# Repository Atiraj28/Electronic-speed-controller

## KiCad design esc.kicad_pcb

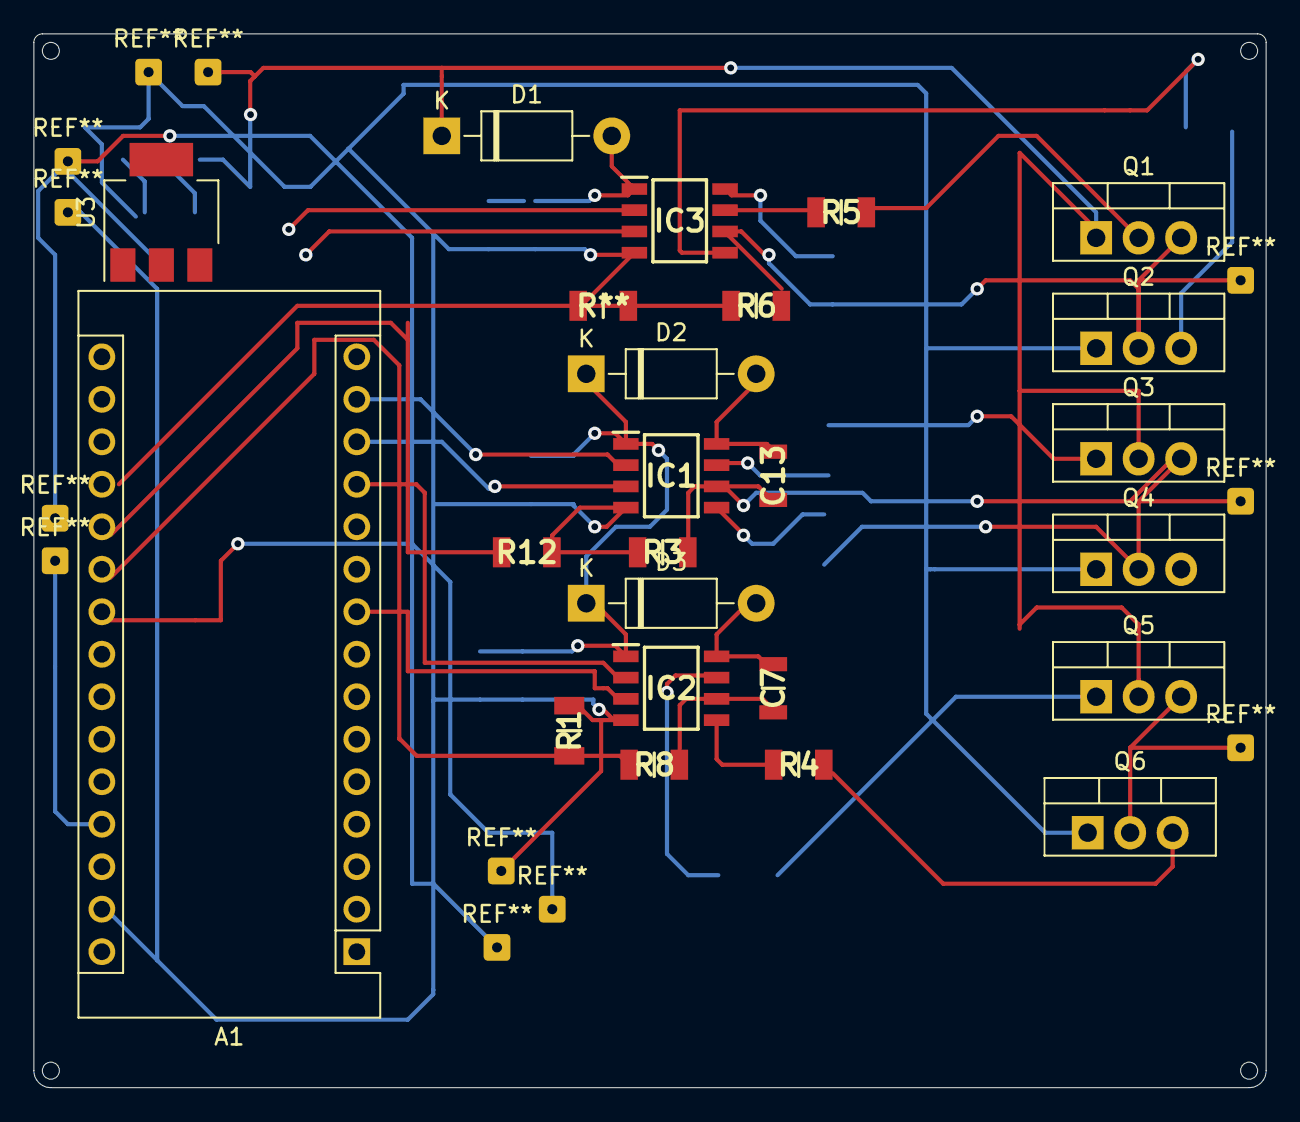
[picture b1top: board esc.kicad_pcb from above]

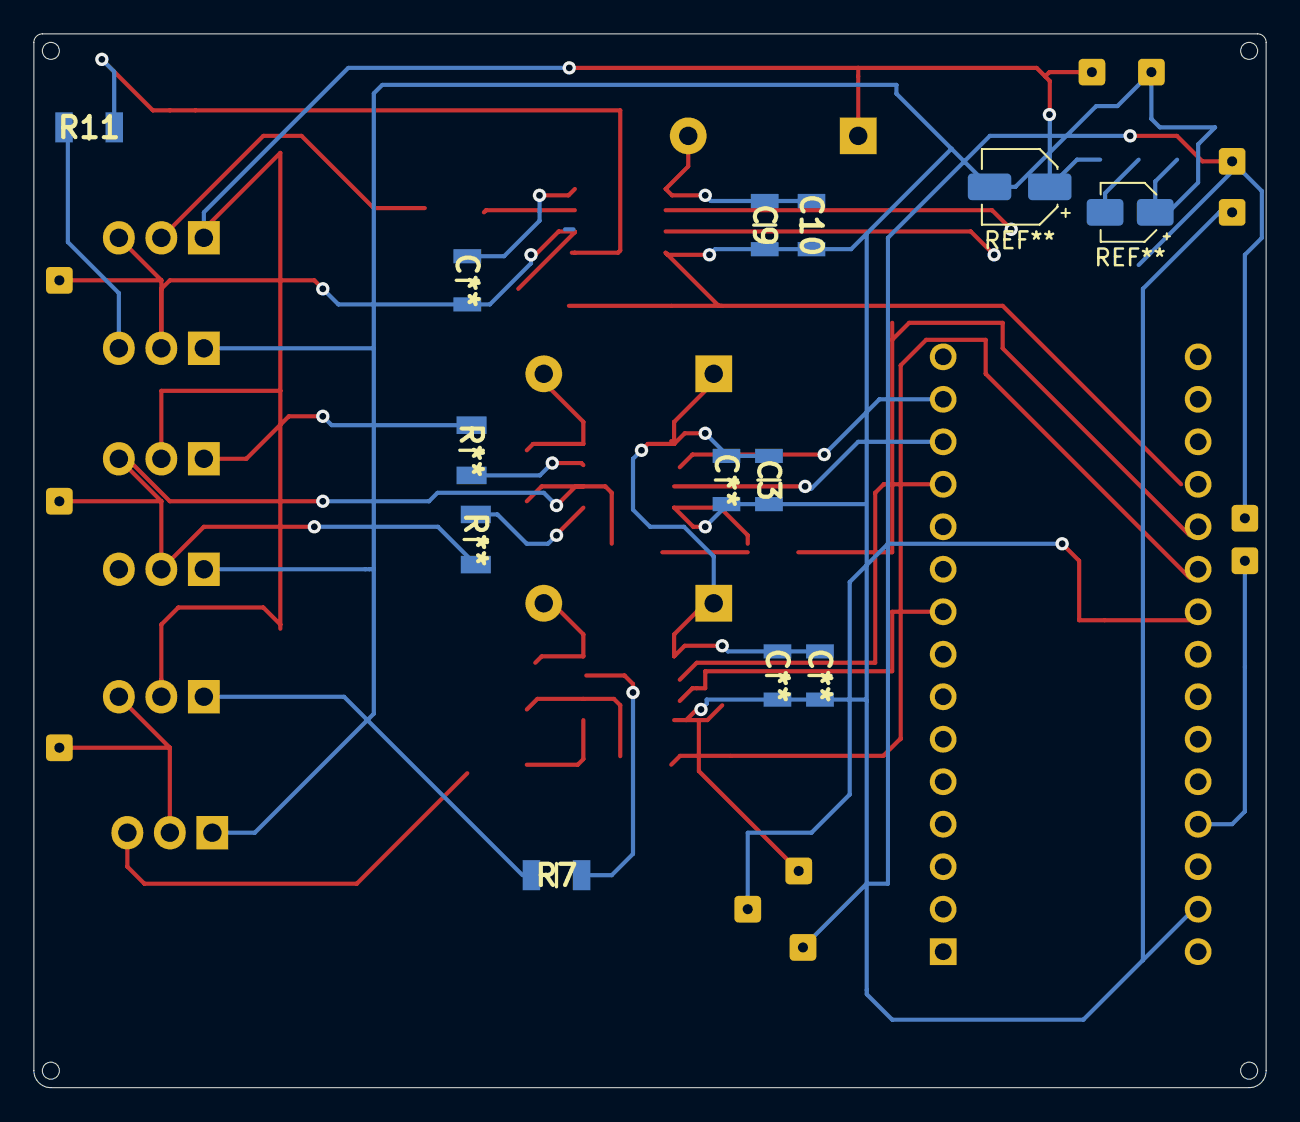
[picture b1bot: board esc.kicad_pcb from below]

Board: 2 copper layers, 73.7 x 63.0 mm, 35 parts (11 on the bottom side), 22 nets.

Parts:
A1: Arduino_Nano_Every; Arduino_Nano
C3, C7, C9, C10, C13: 1206; CAPC3215X163N
C**: CAPC3215X163N
C**#2, C**#3, C**#4: CAPC3215X163N
D1, D2, D3: 1N4001; D_DO-41_SOD81_P10.16mm_Horizontal
IC1, IC2, IC3: IR2301STRPBF; SOIC127P600X175-8N
Q1, Q2, Q3, Q4, Q5, Q6: IRF3205; TO-220-3_Vertical
R1, R3, R4, R5, R6, R7, R8, R11, R12: CRCW12061K00JNTA; RESC3216X60N
R**: RESC3216X60N
R**#2, R**#3: RESC3216X60N
U3: AMS1117-5.0; SOT-223-3_TabPin2

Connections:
+5V: C10.1, U3.2
Earth: C9.2, C10.2, IC1.4, IC2.4, IC3.4, Q2.3, Q4.3, Q6.3, R8.2, R12.1, U3.1
unnamed: A1.4, A1.29
unnamed: C3.1, D1.1, IC1.8
unnamed: C3.2, IC1.6, Q1.3, Q2.2
unnamed: C7.1, D2.1, IC2.8
unnamed: C7.2, IC2.6, Q3.3, Q4.2
unnamed: C13.1, D3.1, IC3.8
unnamed: C13.2, IC3.6, Q5.3, Q6.2
unnamed: IC1.7, R1.1
unnamed: IC2.5, R4.1
unnamed: IC2.7, R3.1
unnamed: IC3.5, R6.1
unnamed: IC3.7, R5.1
unnamed: Q1.1, R1.2
unnamed: Q3.1, R3.2
unnamed: Q4.1, R4.2
unnamed: Q5.1, R5.2
unnamed: Q6.1, R6.2
unnamed: R7.2, R8.1
unnamed: R11.2, R12.2
VDD: C9.1, D1.2, D2.2, D3.2, IC1.1, IC2.1, IC3.1, Q1.2, Q3.2, Q5.2, U3.3
